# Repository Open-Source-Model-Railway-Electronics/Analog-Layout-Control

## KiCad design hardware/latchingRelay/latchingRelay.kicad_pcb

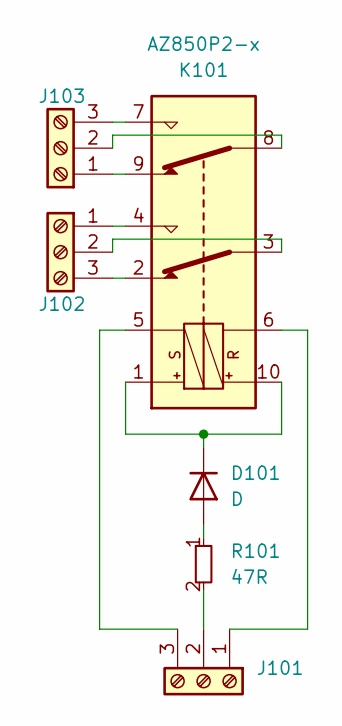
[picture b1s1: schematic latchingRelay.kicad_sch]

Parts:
D101: D; D_DO-34_SOD68_P7.62mm_Horizontal
J101, J102, J103: Screw_Terminal_01x03; PhoenixContact_MC_1,5_3-G-3.5_1x03_P3.50mm_Horizontal; JLCPCB Part# C880573
K101: AZ850P2-x; Relay_DPDT_FRT5
R101: 47R; R_Axial_DIN0204_L3.6mm_D1.6mm_P7.62mm_Horizontal; JLCPCB Part# C17714

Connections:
unnamed: D101.2 (A), R101.1
unnamed: D101.1 (K), K101.1, K101.10
unnamed: J101.1, K101.6
unnamed: J101.2, R101.2
unnamed: J101.3, K101.5
unnamed: J102.1, K101.4
unnamed: J102.2, K101.3
unnamed: J102.3, K101.2
unnamed: J103.1, K101.9
unnamed: J103.2, K101.8
unnamed: J103.3, K101.7

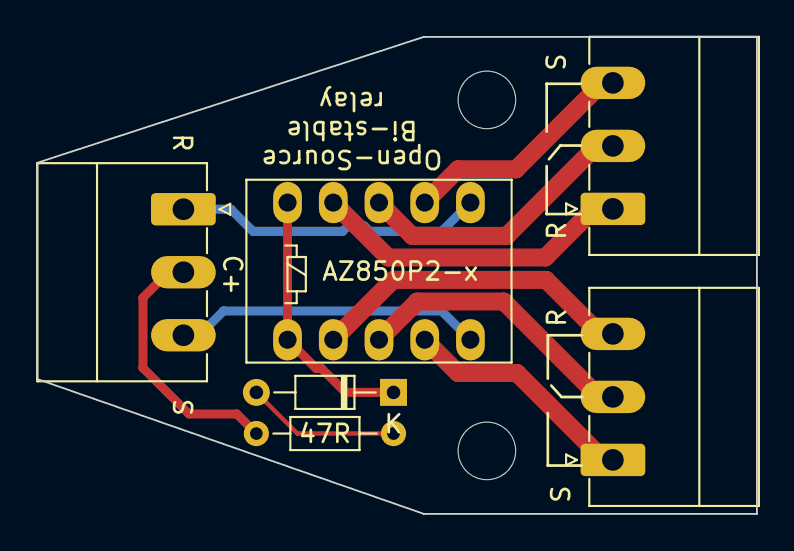
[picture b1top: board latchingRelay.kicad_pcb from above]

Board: 2 copper layers, 40.0 x 26.5 mm, 6 parts (0 on the bottom side), 11 nets.

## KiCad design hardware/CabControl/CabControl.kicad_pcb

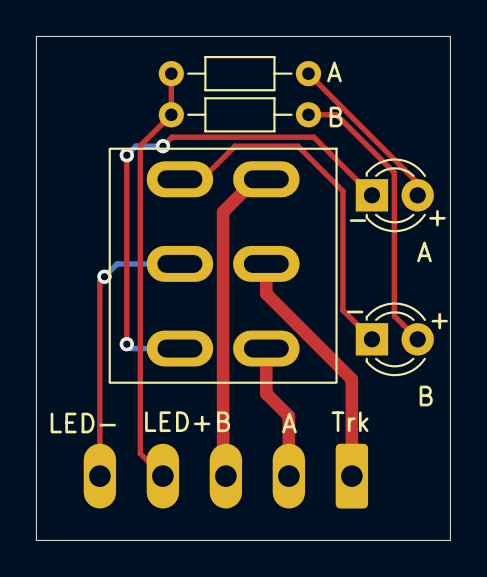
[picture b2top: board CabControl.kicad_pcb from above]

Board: 2 copper layers, 23.0 x 28.0 mm, 6 parts (1 on the bottom side), 9 nets.

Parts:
D1, D2: LED; LED_D3.0mm
J2: Screw_Terminal_01x05; PhoenixContact_MCV_1,5_5-G-3.5_1x05_P3.50mm_Vertical
R1, R2: ???; R_Axial_DIN0204_L3.6mm_D1.6mm_P7.62mm_Horizontal
SW2: MTS203; MTS_DPDT

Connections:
/LED A: D1.1 (K), SW2.6 (C)
/LED B: D2.1 (K), SW2.4 (A)
/spoor: J2.1, SW2.2 (B)
/trafo A: J2.2, SW2.3 (C)
/trafo B: J2.3, SW2.1 (A)
GND: J2.5, SW2.5 (B)
unnamed: D1.2 (A), R1.1
unnamed: D2.2 (A), R2.2
VCC: J2.4, R1.2, R2.1

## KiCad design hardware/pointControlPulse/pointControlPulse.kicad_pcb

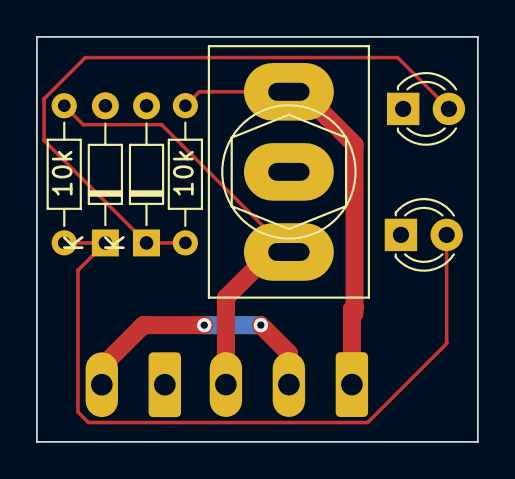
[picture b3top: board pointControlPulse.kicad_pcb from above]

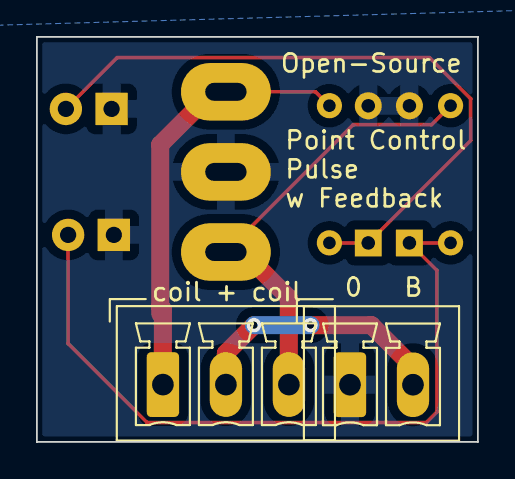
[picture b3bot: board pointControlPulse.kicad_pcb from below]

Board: 2 copper layers, 24.5 x 22.5 mm, 9 parts (2 on the bottom side), 6 nets.

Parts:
D1, D8: D; D_DO-34_SOD68_P7.62mm_Horizontal
D3, D6: LED; LED_D3.0mm
J2: Screw_Terminal_01x03; PhoenixContact_MCV_1,5_3-G-3.5_1x03_P3.50mm_Vertical
J3: Screw_Terminal_01x02; PhoenixContact_MCV_1,5_2-G-3.5_1x02_P3.50mm_Vertical
R1, R2: 10k; R_Axial_DIN0204_L3.6mm_D1.6mm_P7.62mm_Horizontal
SW1: SW_SPDT; SW_Toggle_Blue_wSlots

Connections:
/coil L: J2.3, R1.1, SW1.1 (A)
/coil R: J2.1, R2.1, SW1.3 (C)
GND: D1.2 (A), D3.1 (K), D6.1 (K), D8.2 (A), J3.1, SW1.2 (B)
unnamed: D1.1 (K), D3.2 (A), R1.2
unnamed: D6.2 (A), D8.1 (K), R2.2
VCC: J2.2, J3.2

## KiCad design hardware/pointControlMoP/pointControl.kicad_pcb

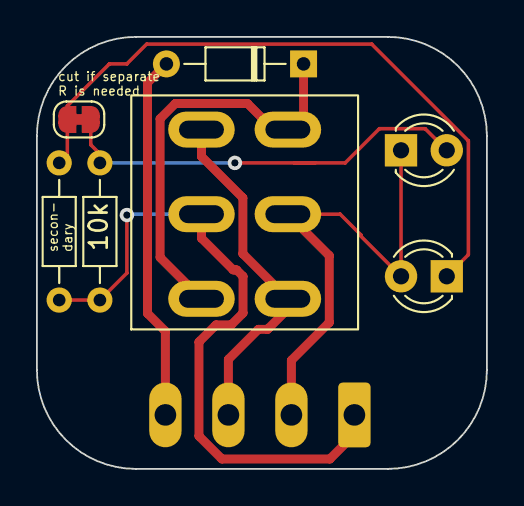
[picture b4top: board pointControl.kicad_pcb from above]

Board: 2 copper layers, 25.0 x 24.0 mm, 8 parts (1 on the bottom side), 7 nets.

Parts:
D1: D; D_DO-34_SOD68_P7.62mm_Horizontal
D_NEG2: LED; LED_D3.0mm
D_POS3: D; LED_D3.0mm
J1: Screw_Terminal_01x04; PhoenixContact_MCV_1,5_4-G-3.5_1x04_P3.50mm_Vertical
JP1: SolderJumper_2_Bridged; SolderJumper-2_P1.3mm_Bridged_RoundedPad1.0x1.5mm
R1, R2: 10k; R_Axial_DIN0204_L3.6mm_D1.6mm_P7.62mm_Horizontal
SW1: SW_Push_DPDT; MTS_DPDT

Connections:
/negIn: J1.3, SW1.3 (C), SW1.4 (A)
/posIn: D1.1 (K), SW1.1 (A), SW1.6 (C)
unnamed: D1.2 (A), J1.4
unnamed: D_NEG2.2 (A), D_POS3.1 (K), J1.2, SW1.5 (B)
unnamed: D_NEG2.1 (K), JP1.1 (A), R1.2
unnamed: D_POS3.2 (A), JP1.2 (B), R2.1
unnamed: J1.1, R1.1, R2.2, SW1.2 (B)

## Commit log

2025-06-19 added board files
2025-06-19 removed release folder from project that was wrongly added. added source files for boards
2025-06-19 Toegevoegd: handleiding (manual.odt)
2025-06-19 Hersteld: handleiding toegevoegd in docs/
